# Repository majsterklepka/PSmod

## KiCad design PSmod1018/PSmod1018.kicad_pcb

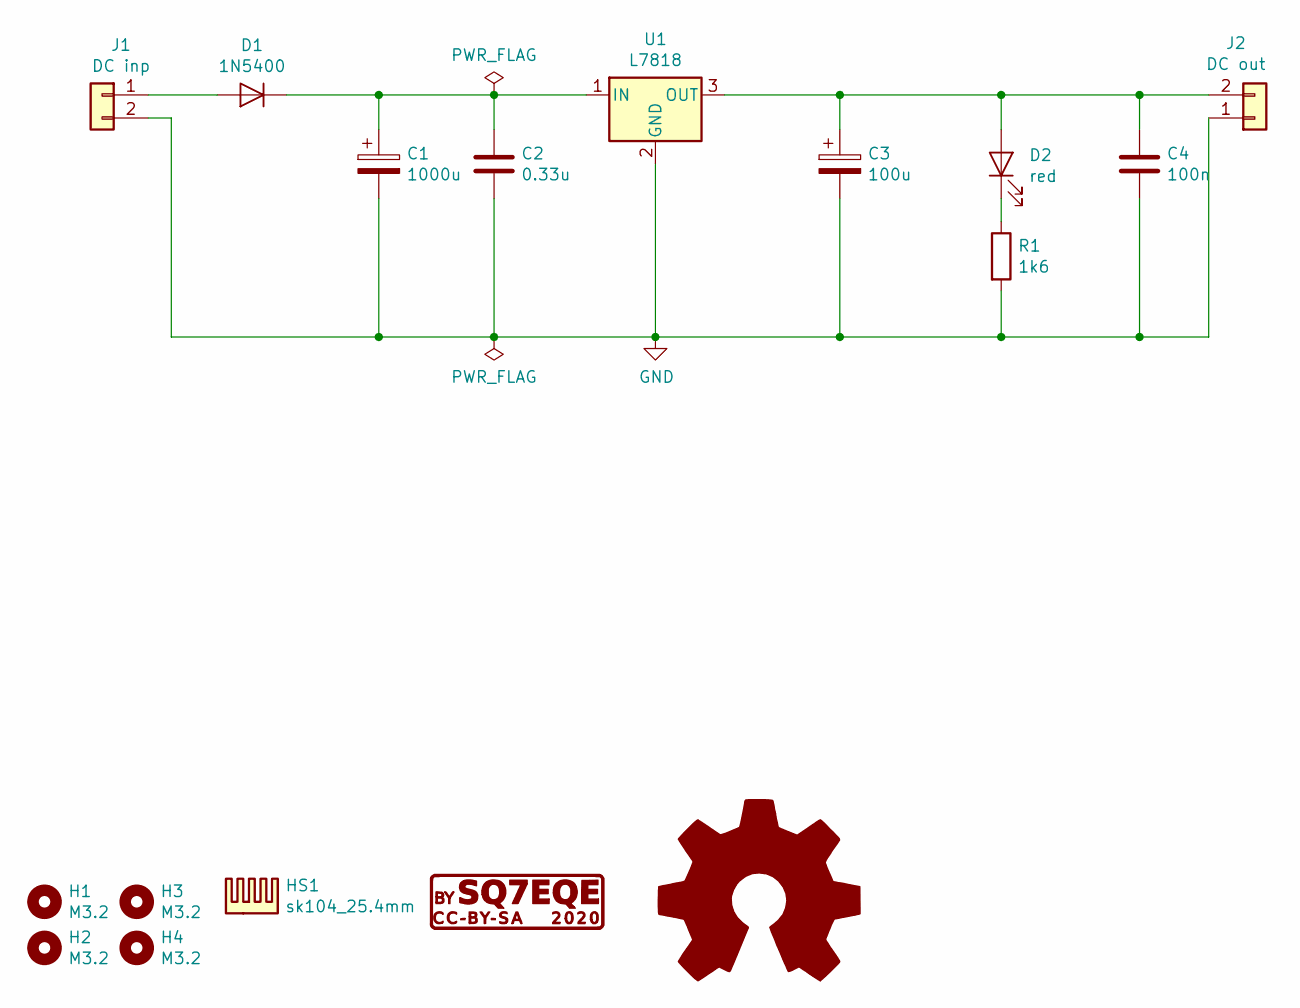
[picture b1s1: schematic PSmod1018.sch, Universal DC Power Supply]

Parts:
C1: 1000u; CP_Radial_D10.0mm_P5.00mm
C2: 0.33u; C_Rect_L7.0mm_W2.5mm_P5.00mm
C3: 100u; CP_Radial_D6.3mm_P2.50mm
C4: 100n; C_Rect_L7.0mm_W2.5mm_P5.00mm
D1: 1N5400; D_DO-201AD_P15.24mm_Horizontal
D2: red; LED_D5.0mm
G1: CC-BY-SA; cc-by-sa
G2: Logo_Open_Hardware_Large; OSHW-Logo2_14.6x12mm_SilkScreen
H1, H2, H3, H4: M3.2; MountingHole_3.2mm_M3
HS1: sk104_25.4mm
J1: DC inp; DG301-5.0-2P
J2: DC out; DG301-5.0-2P
R1: 1k6; R_Axial_DIN0204_L3.6mm_D1.6mm_P7.62mm_Horizontal
U1: L7818; TO-220-3_Vertical

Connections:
GND: C1.2, C2.2, C3.2, C4.2, J1.2, J2.1, R1.2, U1.2 (GND)
unnamed: C1.1, C2.1, D1.1 (K), U1.1 (IN)
unnamed: C3.1, C4.1, D2.2 (A), J2.2, U1.3 (OUT)
unnamed: D1.2 (A), J1.1
unnamed: D2.1 (K), R1.1

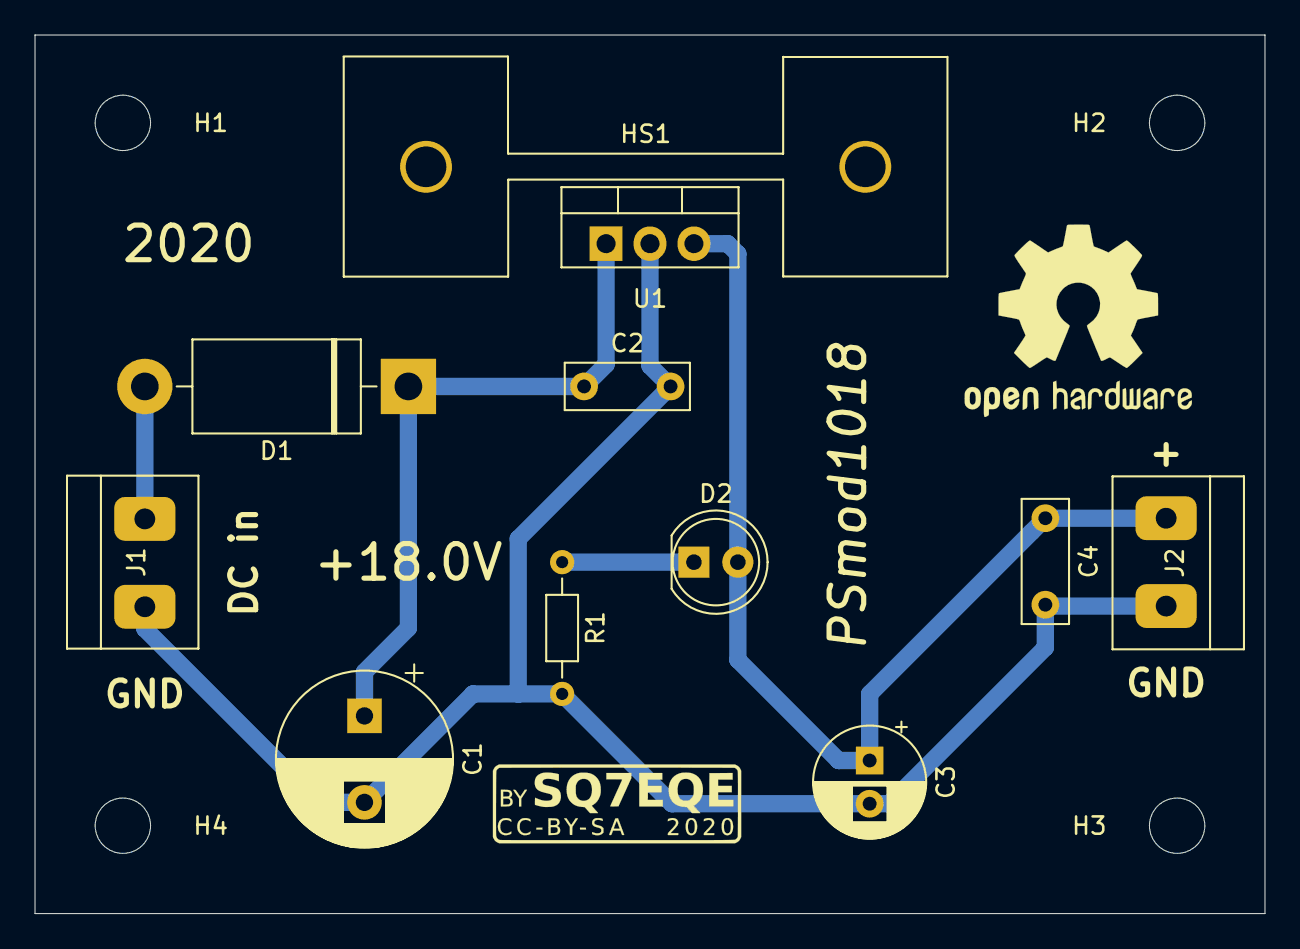
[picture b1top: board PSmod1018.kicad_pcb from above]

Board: 2 copper layers, 71.1 x 50.8 mm, 17 parts (0 on the bottom side), 5 nets.

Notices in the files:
PSmod1018/PSmod1018.kicad_pcb:
CC-BY-SA 4.0
